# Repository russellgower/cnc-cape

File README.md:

CNC Cape for the Beaglebone Black.

Licesed under the Creative Commons Attribution-ShareAlive 4.0 license
<br />This work is licensed under a <a rel="license" href="http://creativecommons.org/licenses/by-sa/4.0/">Creative Commons Attribution-ShareAlike 4.0 International License</a>.

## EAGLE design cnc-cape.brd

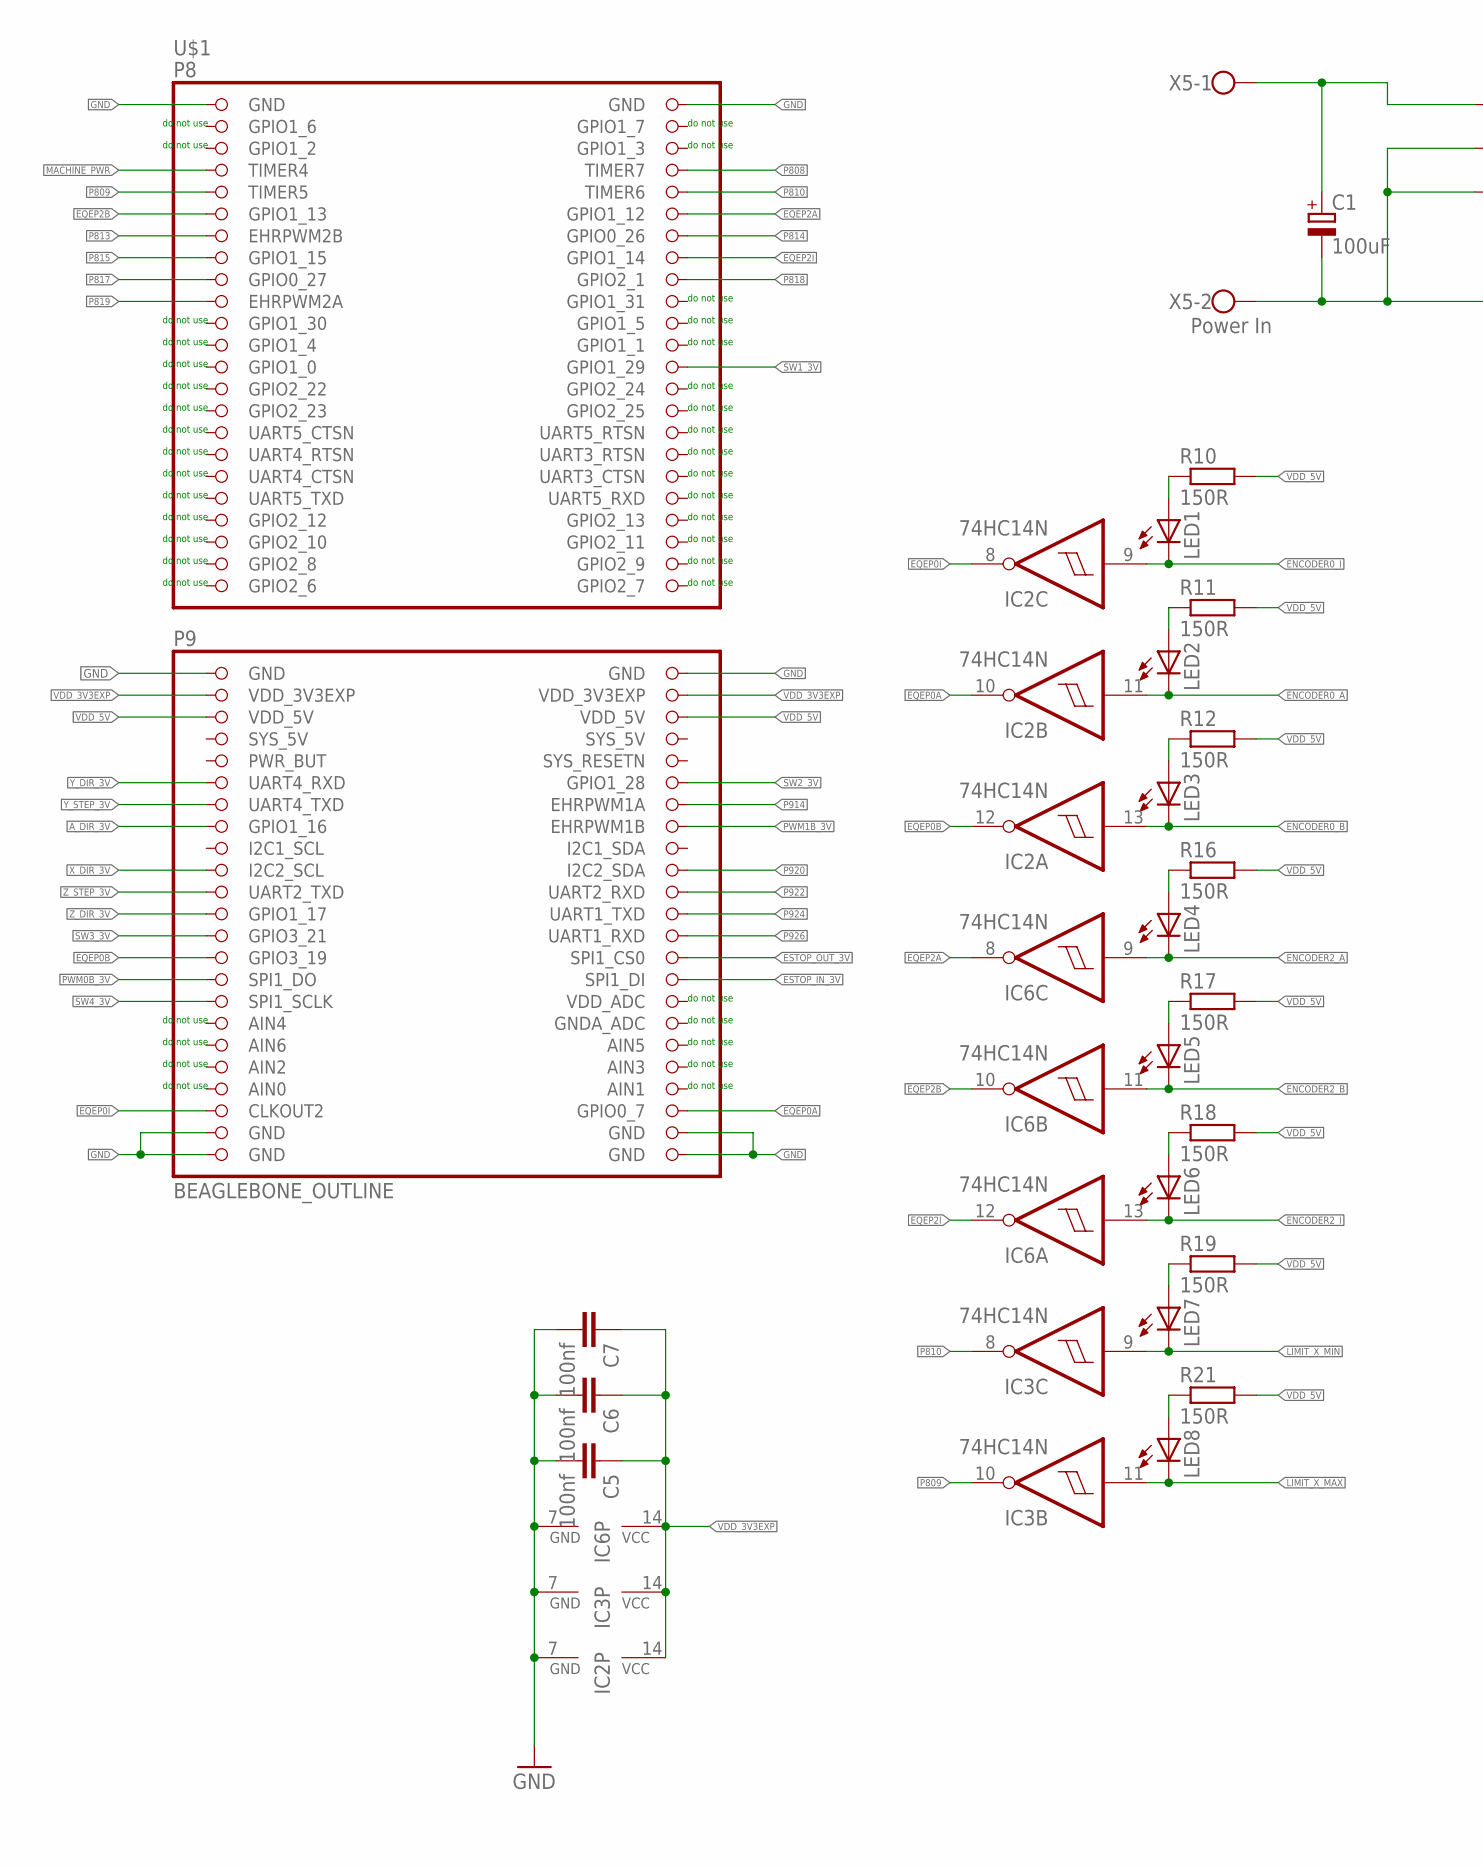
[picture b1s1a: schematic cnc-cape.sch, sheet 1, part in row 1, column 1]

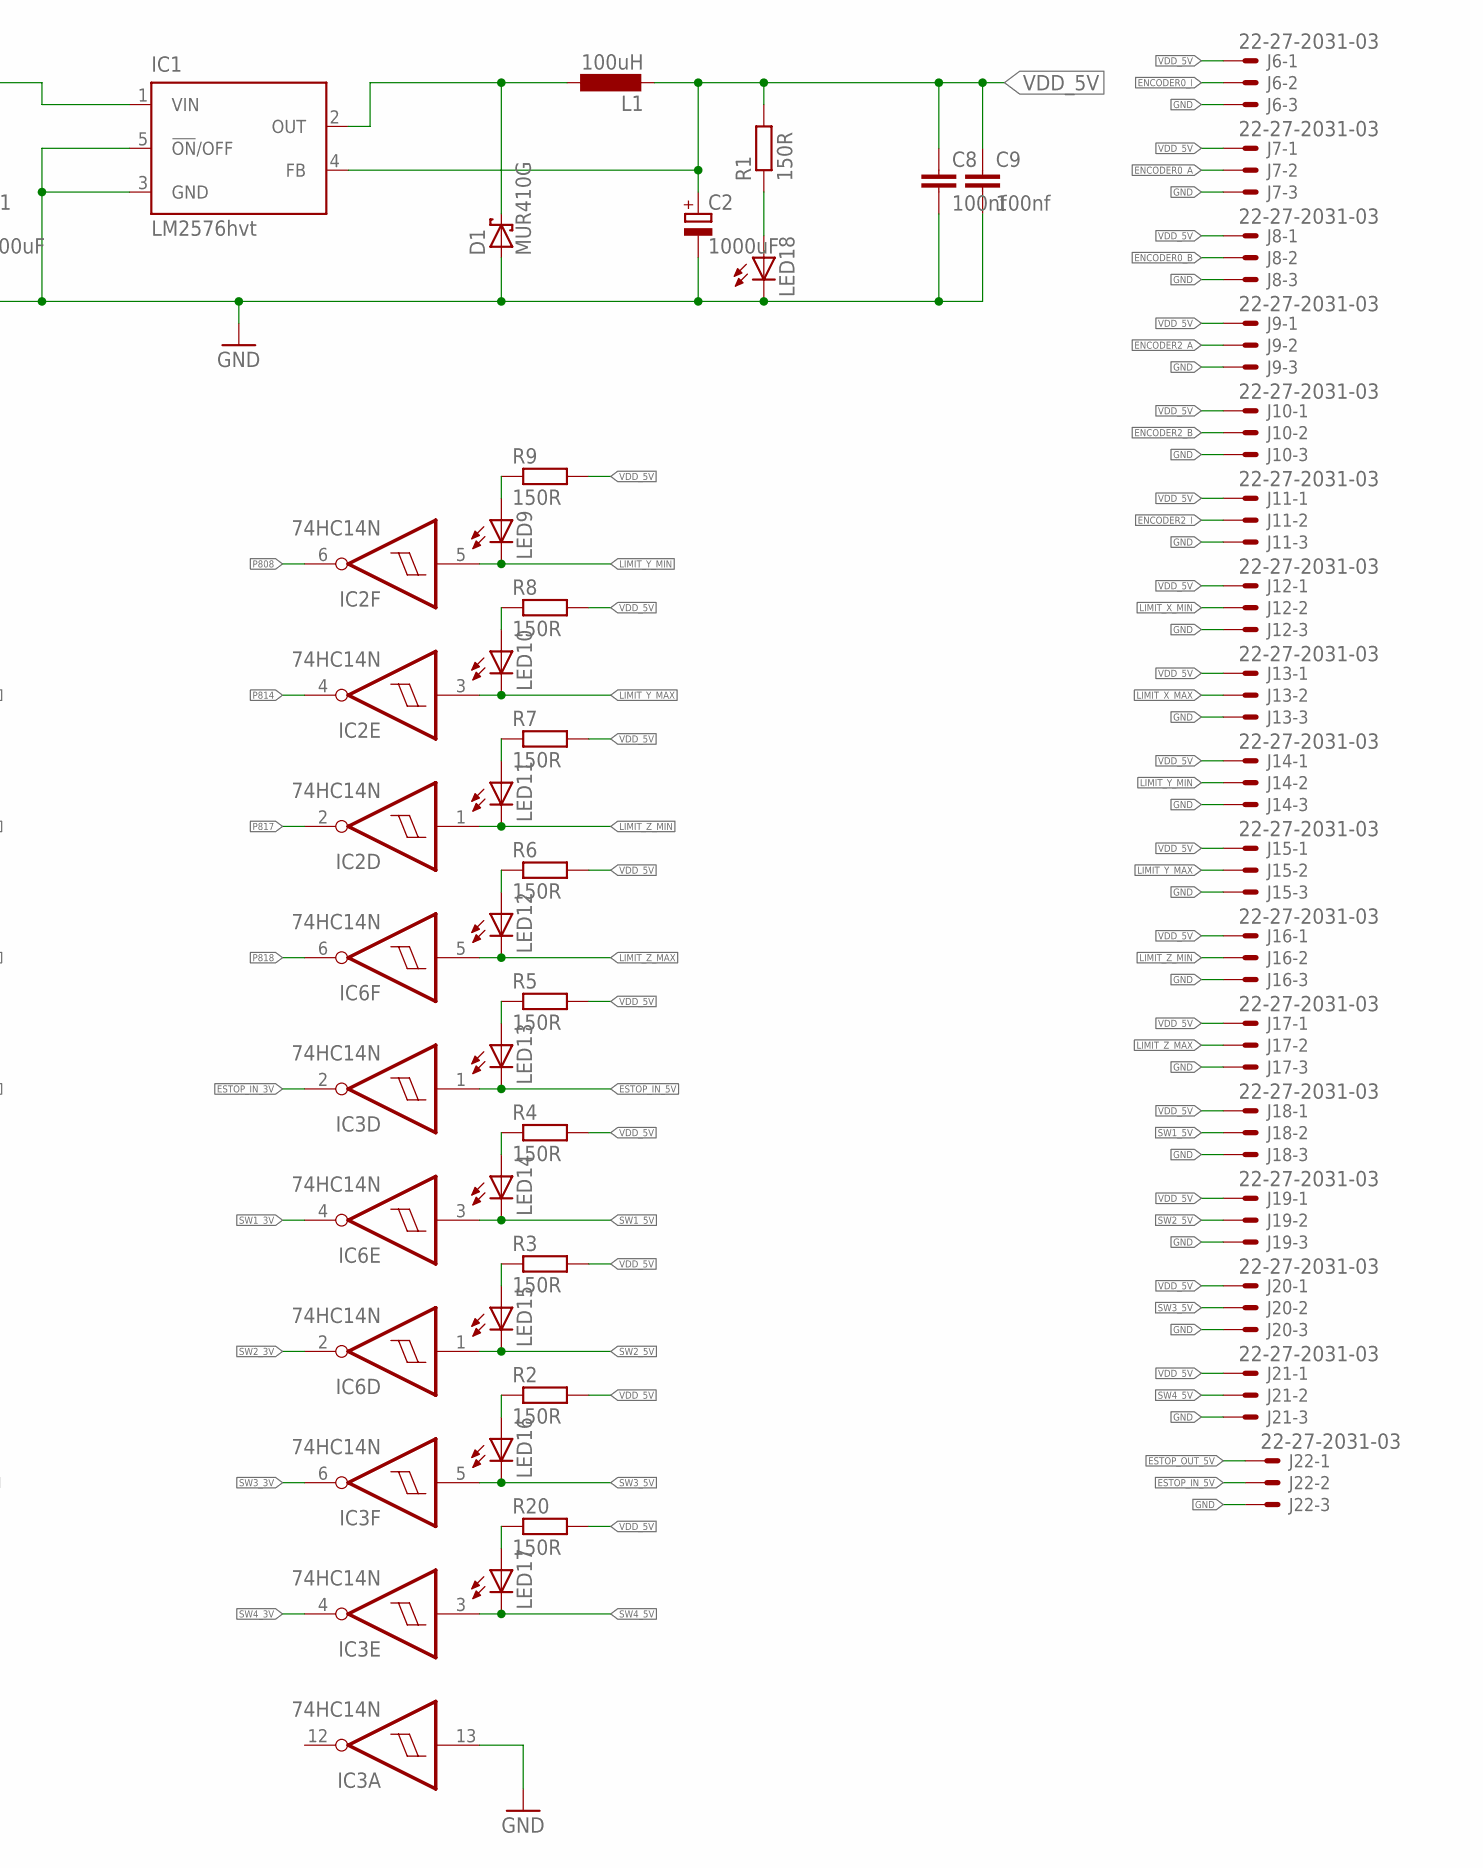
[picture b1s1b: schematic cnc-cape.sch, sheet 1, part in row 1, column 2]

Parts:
C1: 100uF; E5-10,5; FARNELL 1281843
C2: 1000uF; E5-10,5; FARNELL 2346582
C5, C6, C7, C8, C9: 100nf; C050-024X044
D1: MUR410G; DO201T15; FARNELL 1459145
IC1: LM2576hvt; T05D
IC2, IC3, IC6: 74HC14N; DIL14; FARNELL 1739974
J6, J7, J8, J10, J11, J12, J13, J14, J15, J16, J17, J18, J19, J20, J21: 22-27-2031-03; 6410-03; FARNELL 9731156
J9, J22: 22-27-2031-03; 6410-03
L1: 100uH; KM-4.0; FARNELL 1209546
LED1, LED2, LED3, LED4, LED5, LED6, LED7, LED8, LED9, LED10, LED11, LED12, LED13, LED14, LED15, LED16, LED17, LED18: LED3MM; FARNELL 1581133
R1, R2, R3, R4, R5, R6, R7, R8, R9, R10, R11, R12, R16, R17, R18, R19, R20, R21: 150R; 0204/5; FARNELL 1700226
U$1: BEAGLEBONE_OUTLINE; BEAGLEBONE_SHIELD
X5: Power In; W237-102; FARNELL 3089034

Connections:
AIN0: U$1.85 (AIN0)
A_DIR_3V: U$1.61 (GPIO1_16); also elsewhere on the board
ENCODER0_A: IC2.11 (I), J7.2, LED2.K (C)
ENCODER0_B: IC2.13 (I), J8.2, LED3.K (C)
ENCODER0_I: IC2.9 (I), J6.2, LED1.K (C)
ENCODER2_A: IC6.9 (I), J9.2, LED4.K (C)
ENCODER2_B: IC6.11 (I), J10.2, LED5.K (C)
ENCODER2_I: IC6.13 (I), J11.2, LED6.K (C)
EQEP0A: IC2.10 (O), U$1.88 (GPIO0_7)
EQEP0B: IC2.12 (O), U$1.73 (GPIO3_19)
EQEP0I: IC2.8 (O), U$1.87 (CLKOUT2)
EQEP2A: IC6.8 (O), U$1.12 (GPIO1_12)
EQEP2B: IC6.10 (O), U$1.11 (GPIO1_13)
EQEP2I: IC6.12 (O), U$1.16 (GPIO1_14)
ESTOP_IN_3V: IC3.2 (O), U$1.76 (SPI1_DI)
ESTOP_IN_5V: IC3.1 (I), J22.2, LED13.K (C); also elsewhere on the board
ESTOP_OUT_3V: U$1.74 (SPI1_CS0); also elsewhere on the board
ESTOP_OUT_5V: J22.1; also elsewhere on the board
GND: C1.-, C2.-, C5.2, C6.2, C7.2, C8.2, C9.2, D1.A, IC1.3 (GND), IC1.5 (!ON!/OFF), IC2.7 (GND), IC3.7 (GND), IC3.13 (I), IC6.7 (GND), J6.3, J7.3, J8.3, J9.3, J10.3, J11.3, J12.3, J13.3, J14.3, J15.3, J16.3, J17.3, J18.3, J19.3, J20.3, J21.3, J22.3, LED18.K (C), U$1.1 (GND), U$1.2 (GND), U$1.47 (GND), U$1.48 (GND), U$1.89 (GND), U$1.90 (GND), U$1.91 (GND), U$1.92 (GND), X5.2; also elsewhere on the board
LIMIT_X_MAX: IC3.11 (I), J13.2, LED8.K (C)
LIMIT_X_MIN: IC3.9 (I), J12.2, LED7.K (C)
LIMIT_Y_MAX: IC2.3 (I), J15.2, LED10.K (C)
LIMIT_Y_MIN: IC2.5 (I), J14.2, LED9.K (C)
LIMIT_Z_MAX: IC6.5 (I), J17.2, LED12.K (C)
LIMIT_Z_MIN: IC2.1 (I), J16.2, LED11.K (C)
MACHINE_PWR: U$1.7 (TIMER4); also elsewhere on the board
unnamed: LED8.A, R21.1
unnamed: LED7.A, R19.1
unnamed: D1.C, IC1.2 (OUT), L1.P$1 (1)
unnamed: LED6.A, R18.1
unnamed: LED5.A, R17.1
unnamed: LED4.A, R16.1
unnamed: LED16.A, R2.1
unnamed: LED15.A, R3.1
unnamed: LED14.A, R4.1
unnamed: LED13.A, R5.1
unnamed: LED12.A, R6.1
unnamed: LED3.A, R12.1
unnamed: LED2.A, R11.1
unnamed: LED1.A, R10.1
unnamed: LED9.A, R9.1
unnamed: LED10.A, R8.1
unnamed: LED11.A, R7.1
unnamed: LED17.A, R20.1
unnamed: LED18.A, R1.1
P808: IC2.6 (O), U$1.8 (TIMER7)
P809: IC3.10 (O), U$1.9 (TIMER5)
P810: IC3.8 (O), U$1.10 (TIMER6)
P813: U$1.13 (EHRPWM2B); also elsewhere on the board
P814: IC2.4 (O), U$1.14 (GPIO0_26)
P815: U$1.15 (GPIO1_15); also elsewhere on the board
P817: IC2.2 (O), U$1.17 (GPIO0_27)
P818: IC6.6 (O), U$1.18 (GPIO2_1)
P819: U$1.19 (EHRPWM2A); also elsewhere on the board
P914: U$1.60 (EHRPWM1A); also elsewhere on the board
P920: U$1.66 (I2C2_SDA); also elsewhere on the board
P922: U$1.68 (UART2_RXD); also elsewhere on the board
P924: U$1.70 (UART1_TXD); also elsewhere on the board
P926: U$1.72 (UART1_RXD); also elsewhere on the board
PWM0B_3V: U$1.75 (SPI1_DO); also elsewhere on the board
PWM1B_3V: U$1.62 (EHRPWM1B); also elsewhere on the board
SW1_3V: IC6.4 (O), U$1.26 (GPIO1_29)
SW1_5V: IC6.3 (I), J18.2, LED14.K (C)
SW2_3V: IC6.2 (O), U$1.58 (GPIO1_28)
SW2_5V: IC6.1 (I), J19.2, LED15.K (C)
SW3_3V: IC3.6 (O), U$1.71 (GPIO3_21)
SW3_5V: IC3.5 (I), J20.2, LED16.K (C)
SW4_3V: IC3.4 (O), U$1.77 (SPI1_SCLK)
SW4_5V: IC3.3 (I), J21.2, LED17.K (C)
SYS_5V: U$1.53 (SYS_5V)
VCC: C1.+, IC1.1 (VIN), X5.1
VDD_3V3EXP: C5.1, C6.1, C7.1, IC2.14 (VCC), IC3.14 (VCC), IC6.14 (VCC), U$1.49 (VDD_3V3EXP), U$1.50 (VDD_3V3EXP)
VDD_5V: C2.+, C8.1, C9.1, IC1.4 (FB), J6.1, J7.1, J8.1, J9.1, J10.1, J11.1, J12.1, J13.1, J14.1, J15.1, J16.1, J17.1, J18.1, J19.1, J20.1, J21.1, L1.P$2 (2), R1.2, R2.2, R3.2, R4.2, R5.2, R6.2, R7.2, R8.2, R9.2, R10.2, R11.2, R12.2, R16.2, R17.2, R18.2, R19.2, R20.2, R21.2, U$1.51 (VDD_5V), U$1.52 (VDD_5V); also elsewhere on the board
X_DIR_3V: U$1.65 (I2C2_SCL); also elsewhere on the board
Y_DIR_3V: U$1.57 (UART4_RXD); also elsewhere on the board
Y_STEP_3V: U$1.59 (UART4_TXD); also elsewhere on the board
Z_DIR_3V: U$1.69 (GPIO1_17); also elsewhere on the board
Z_STEP_3V: U$1.67 (UART2_TXD); also elsewhere on the board

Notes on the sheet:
do not use

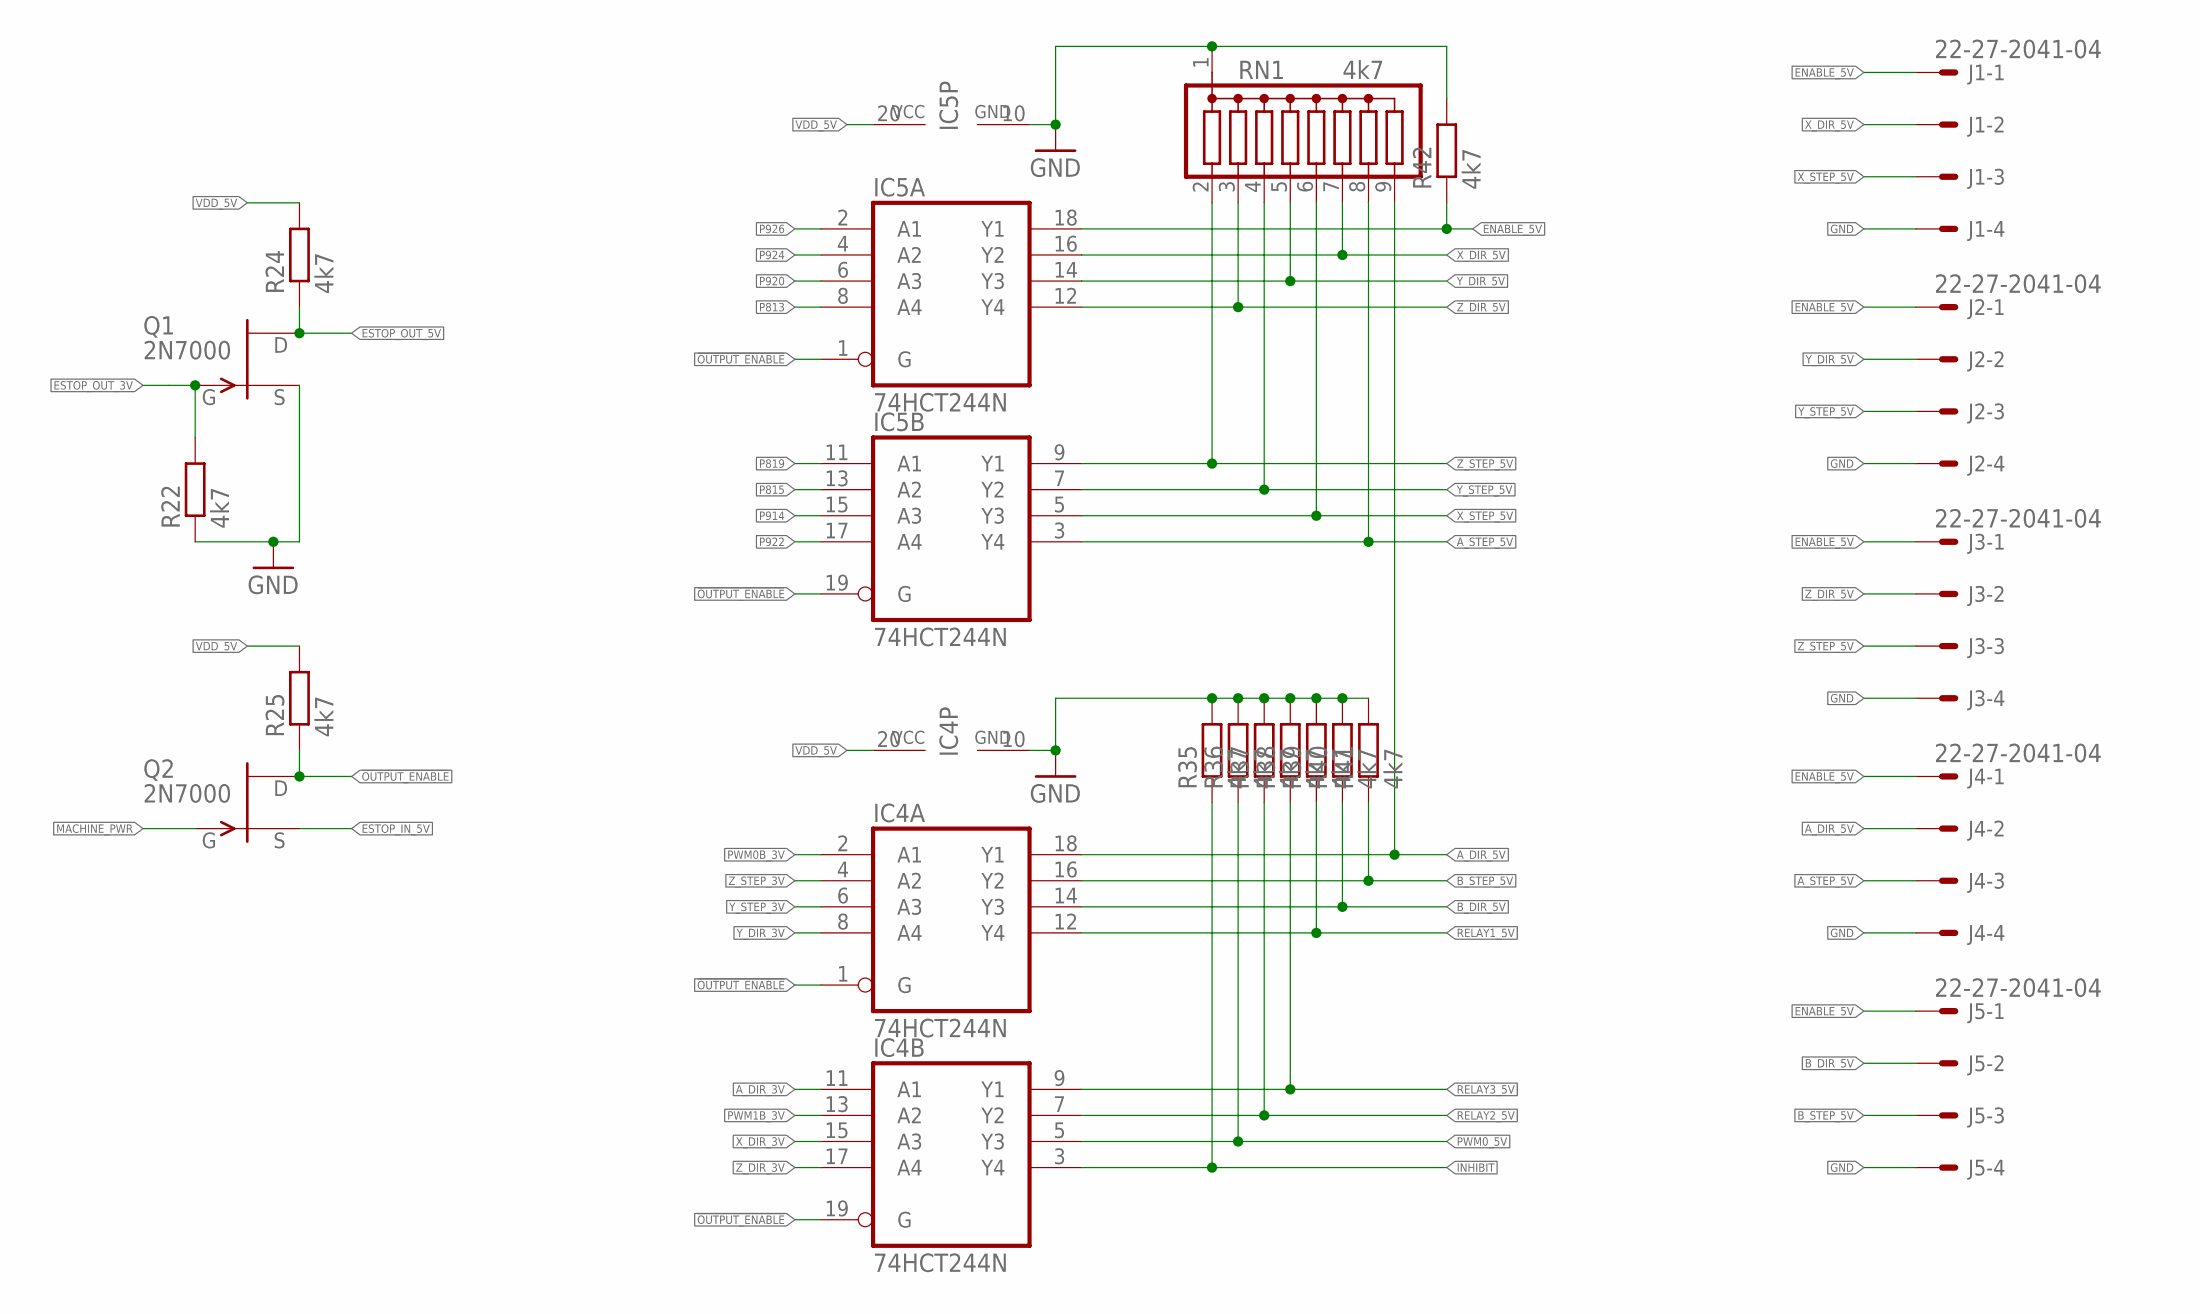
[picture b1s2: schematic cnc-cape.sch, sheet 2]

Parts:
IC4, IC5: 74HCT244N; DIL20; FARNELL 382267
J1, J2, J3, J4, J5: 22-27-2041-04; 6410-04; FARNELL 9731164
Q1, Q2: 2N7000; TO92; FARNELL 9845178
R22, R24, R25: 4k7; 0204/5; FARNELL 1700245
R35, R36, R37, R38, R39, R40, R41, R42: 4k7; 0204/5
RN1: 4k7; SIL9; FARNELL 9357025

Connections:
!OUTPUT_ENABLE!: IC4.1 (G), IC4.19 (G), IC5.1 (G), IC5.19 (G), Q2.1 (D), R25.1
A_DIR_3V: IC4.11 (A1); also elsewhere on the board
A_DIR_5V: IC4.18 (Y1), J4.2, RN1.9
A_STEP_5V: IC5.3 (Y4), J4.3, RN1.8
B_DIR_5V: IC4.14 (Y3), J5.2, R40.1
B_STEP_5V: IC4.16 (Y2), J5.3, R41.1
ENABLE_5V: IC5.18 (Y1), J1.1, J2.1, J3.1, J4.1, J5.1, R42.1
ESTOP_IN_5V: Q2.3 (S); also elsewhere on the board
ESTOP_OUT_3V: Q1.2 (G), R22.2; also elsewhere on the board
ESTOP_OUT_5V: Q1.1 (D), R24.1; also elsewhere on the board
GND: IC4.10 (GND), IC5.10 (GND), J1.4, J2.4, J3.4, J4.4, J5.4, Q1.3 (S), R22.1, R35.2, R36.2, R37.2, R38.2, R39.2, R40.2, R41.2, R42.2, RN1.1; also elsewhere on the board
INHIBIT: IC4.3 (Y4), R35.1; also elsewhere on the board
MACHINE_PWR: Q2.2 (G); also elsewhere on the board
P813: IC5.8 (A4); also elsewhere on the board
P815: IC5.13 (A2); also elsewhere on the board
P819: IC5.11 (A1); also elsewhere on the board
P914: IC5.15 (A3); also elsewhere on the board
P920: IC5.6 (A3); also elsewhere on the board
P922: IC5.17 (A4); also elsewhere on the board
P924: IC5.4 (A2); also elsewhere on the board
P926: IC5.2 (A1); also elsewhere on the board
PWM0B_3V: IC4.2 (A1); also elsewhere on the board
PWM0_5V: IC4.5 (Y3), R36.1; also elsewhere on the board
PWM1B_3V: IC4.13 (A2); also elsewhere on the board
RELAY1_5V: IC4.12 (Y4), R39.1; also elsewhere on the board
RELAY2_5V: IC4.7 (Y2), R37.1; also elsewhere on the board
RELAY3_5V: IC4.9 (Y1), R38.1; also elsewhere on the board
VDD_5V: IC4.20 (VCC), IC5.20 (VCC), R24.2, R25.2; also elsewhere on the board
X_DIR_3V: IC4.15 (A3); also elsewhere on the board
X_DIR_5V: IC5.16 (Y2), J1.2, RN1.7
X_STEP_5V: IC5.5 (Y3), J1.3, RN1.6
Y_DIR_3V: IC4.8 (A4); also elsewhere on the board
Y_DIR_5V: IC5.14 (Y3), J2.2, RN1.5
Y_STEP_3V: IC4.6 (A3); also elsewhere on the board
Y_STEP_5V: IC5.7 (Y2), J2.3, RN1.4
Z_DIR_3V: IC4.17 (A4); also elsewhere on the board
Z_DIR_5V: IC5.12 (Y4), J3.2, RN1.3
Z_STEP_3V: IC4.4 (A2); also elsewhere on the board
Z_STEP_5V: IC5.9 (Y1), J3.3, RN1.2

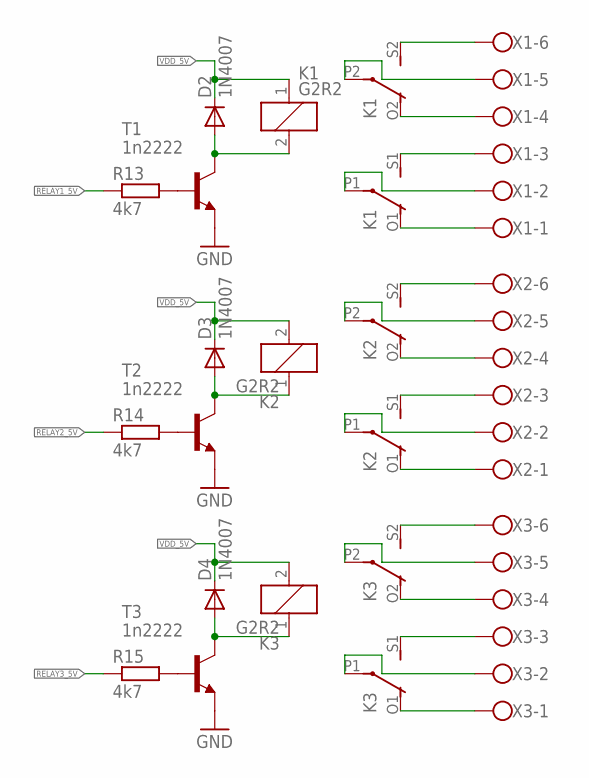
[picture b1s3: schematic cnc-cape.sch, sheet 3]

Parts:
D2, D3, D4: 1N4007; DO41-10; FARNELL 9565051
K1, K2, K3: G2R2; FARNELL 1703716
R13, R14, R15: 4k7; 0204/5; FARNELL 1700245
T1, T2, T3: 1n2222; TO92; FARNELL 1611371
X1, X2, X3: W237-6; FARNELL 3089071

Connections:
GND: T1.1 (E), T2.1 (E), T3.1 (E); also elsewhere on the board
unnamed: R13.2, T1.2 (B)
unnamed: D2.A, K1.2, T1.3 (C)
unnamed: K1.S2 (S), X1.6
unnamed: K1.O2 (O), X1.4
unnamed: K1.P2, X1.5
unnamed: K1.S1 (S), X1.3
unnamed: K1.P1, X1.2
unnamed: K1.O1 (O), X1.1
unnamed: R14.2, T2.2 (B)
unnamed: D3.A, K2.1, T2.3 (C)
unnamed: K2.S2 (S), X2.6
unnamed: K2.O2 (O), X2.4
unnamed: K2.P2, X2.5
unnamed: K2.S1 (S), X2.3
unnamed: K2.P1, X2.2
unnamed: K2.O1 (O), X2.1
unnamed: R15.2, T3.2 (B)
unnamed: D4.A, K3.1, T3.3 (C)
unnamed: K3.S2 (S), X3.6
unnamed: K3.O2 (O), X3.4
unnamed: K3.P2, X3.5
unnamed: K3.S1 (S), X3.3
unnamed: K3.P1, X3.2
unnamed: K3.O1 (O), X3.1
RELAY1_5V: R13.1; also elsewhere on the board
RELAY2_5V: R14.1; also elsewhere on the board
RELAY3_5V: R15.1; also elsewhere on the board
VDD_5V: D2.C, D3.C, D4.C, K1.1, K2.2, K3.2; also elsewhere on the board

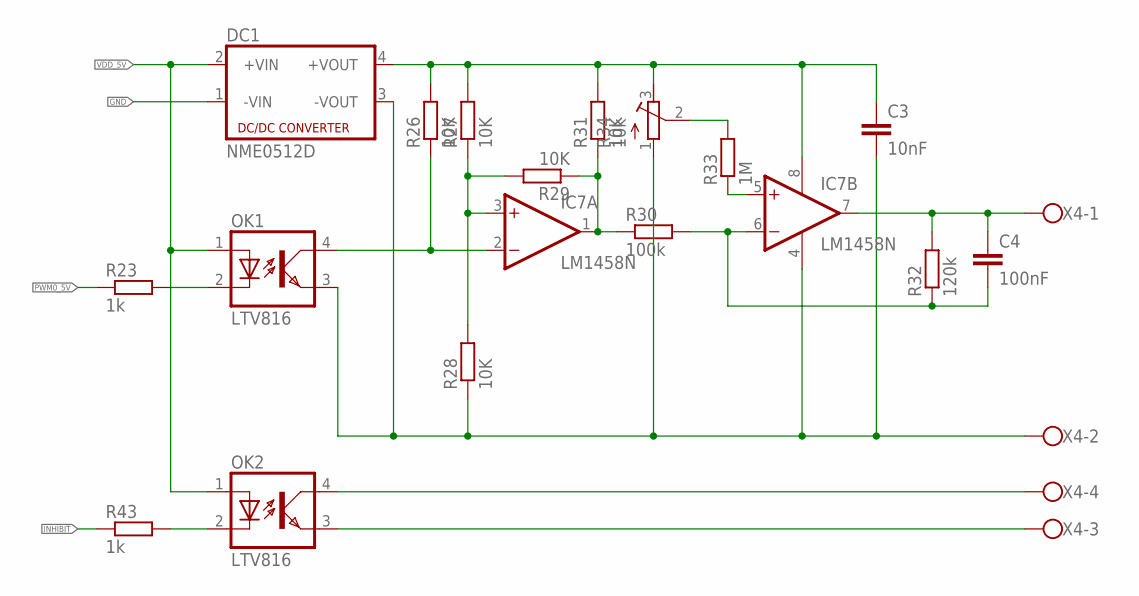
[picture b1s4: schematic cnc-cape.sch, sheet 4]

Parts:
C3: 10nF; C050-024X044
C4: 100nF; C050-024X044
DC1: NME0512D; NME; FARNELL 1021457
IC7: LM1458N; DIL08
OK1, OK2: LTV816; DIL04
R23, R43: 1k; 0204/5
R26, R27, R28, R29, R31: 10K; 0204/5; FARNELL 1700251
R30: 100k; 0204/5
R32: 120k; 0204/5
R33: 1M; 0204/5
R34: 10k; RTRIM64P
X4: W237-4

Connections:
GND: DC1.1 (-VIN); also elsewhere on the board
INHIBIT: R43.1; also elsewhere on the board
unnamed: C3.1, DC1.4 (+VOUT), IC7.8 (V+), R26.2, R27.2, R31.2, R34.3 (E)
unnamed: OK1.2 (C), R23.2
unnamed: OK2.4 (COL), X4.4
unnamed: IC7.2 (-IN), OK1.4 (COL), R26.1
unnamed: IC7.3 (+IN), R27.1, R28.2, R29.2
unnamed: IC7.1 (OUT), R29.1, R30.1, R31.1
unnamed: C4.2, IC7.6 (-IN), R30.2, R32.1
unnamed: OK2.3 (EMIT), X4.3
unnamed: OK2.2 (C), R43.2
unnamed: IC7.5 (+IN), R33.1
unnamed: R33.2, R34.2 (S)
PWM0_5V: R23.1; also elsewhere on the board
SPINDLE+: C4.1, IC7.7 (OUT), R32.2, X4.1
SPINDLE-: C3.2, DC1.3 (-VOUT), IC7.4 (V-), OK1.3 (EMIT), R28.1, R34.1 (A), X4.2
VDD_5V: DC1.2 (+VIN), OK1.1 (A), OK2.1 (A); also elsewhere on the board

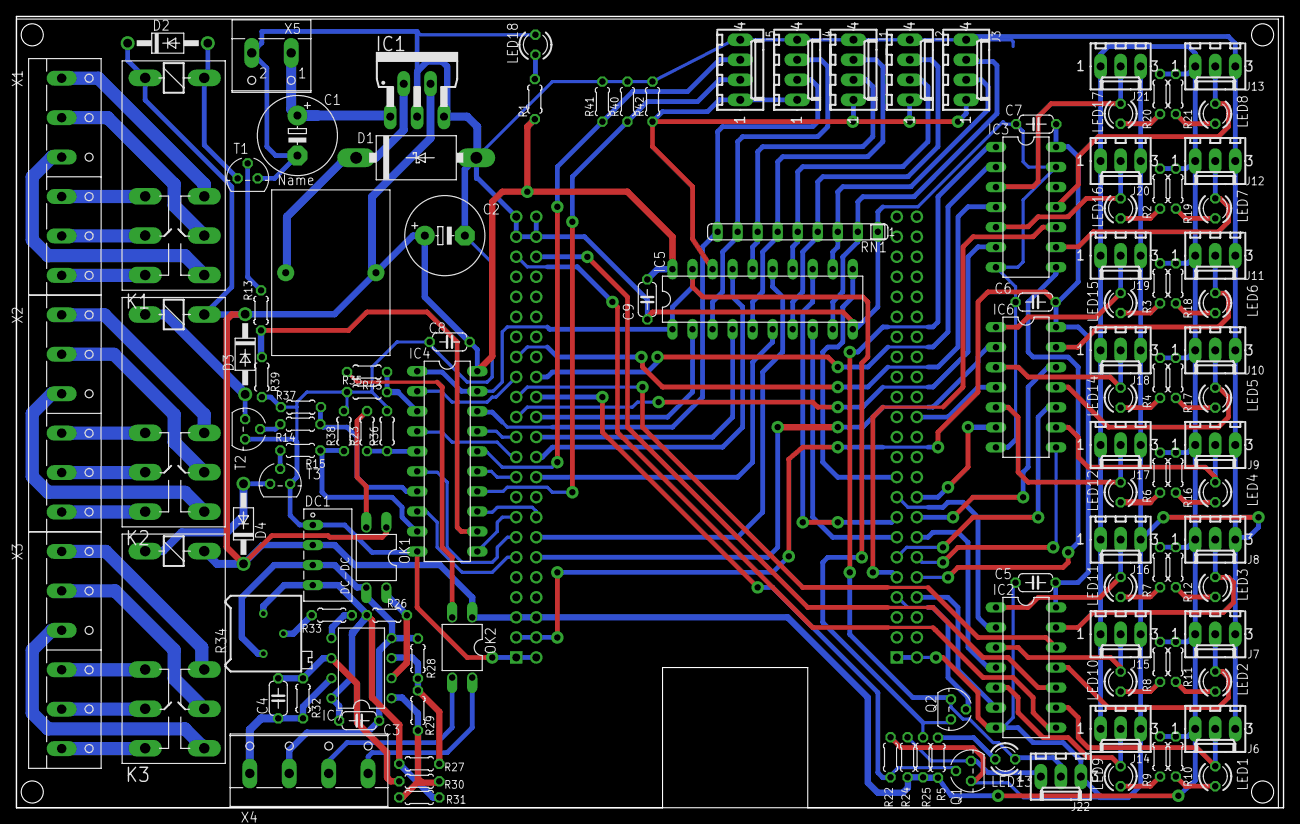
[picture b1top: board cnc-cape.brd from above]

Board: 2 copper layers, 160.7 x 100.3 mm, 122 parts (1 on the bottom side), 130 nets.

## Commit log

2015-03-25 Rearraged layout to reduce via count
2015-04-09 Fixed pwm polarity
2015-04-09 Added opto coupled inhibit out put, to disable spindle driver
2015-07-19 fixed some net names
2015-07-19 added license
